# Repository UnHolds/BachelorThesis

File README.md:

# Bachelor Thesis

This is the repository of my bachelor thesis for the Software Engineering
bachelor at TU-Vienna.

## Structure

```
.
├── Code/
│   ├── AmpelSchaltung
│   ├── AudioBuffer
│   ├── AudioPlayer
│   ├── ExperimentI2CSpeakerSystem
│   ├── ExperimentNandGatter
│   ├── ExperimentNandGatter2
│   ├── ExperimentNandGatterDACControl
│   └── I2CSpeakerSystemSDCard
├── FreeCAD/
│   ├── Ampel
│   ├── AudioController
│   ├── Speaker_Housing
│   └── ...
├── KiCAD/
│   ├── AmpelSchaltung
│   ├── AudioController
│   ├── CabelAdapter
│   ├── ExperimentNAND
│   └── Speaker
├── LtSpice/
│   ├── Metastabile-NAND-Gatter
│   ├── i2c_speaker_amp
│   └── models
├── Tools
├── bachelorThesisObsidian
├── latex
└── slides
```

- `Code`: Contains the firmware of the different prototypes, the most important firmware are:
  - `AmpelSchaltung`: Firmware for the Ampelschaltung
  - `AudioBuffer`: Firmware of the audio buffer on the audio control PCB
  - `AudioPlayer`: Firmware of the audio player on the audio control PCB
- `FreeCAD`: contains the housing of the different demonstrators, and also 3D models that where used in assemblies.
  - `Ampel`: housing for the Ampelschaltung
  - `AudioController`: housing of the controller part of the audio demonstrator
  - `Speaker_Housing`: housing of the speaker part of the audio demonstrator
- `KiCAD`: contains the schematics and the PCB of the demonstrators
- `LtSpice`: contains the simulations and also the LtSpice model of the DAC.
- `Tools`: contains the tools that were used to evaluated data, display data or to generate audio files (`.bwav`)
- `bachelorThesisObsidian`: contains a lot of addition information and the development process. Can be seen as an extension of the thesis. To view the files it is encouraged to use [obsidian](https://obsidian.md/), but is also possible to just view the plain markdown files.
- `latex`: contains the raw latex files to build the thesis
- `slides`: contains the slides that are used in the prolog. (Important: This is a submodule and one needs to have access rights to the prolog repo to clone this repository)

# Demonstrators:

## Ampelschaltung

## Audioschaltung

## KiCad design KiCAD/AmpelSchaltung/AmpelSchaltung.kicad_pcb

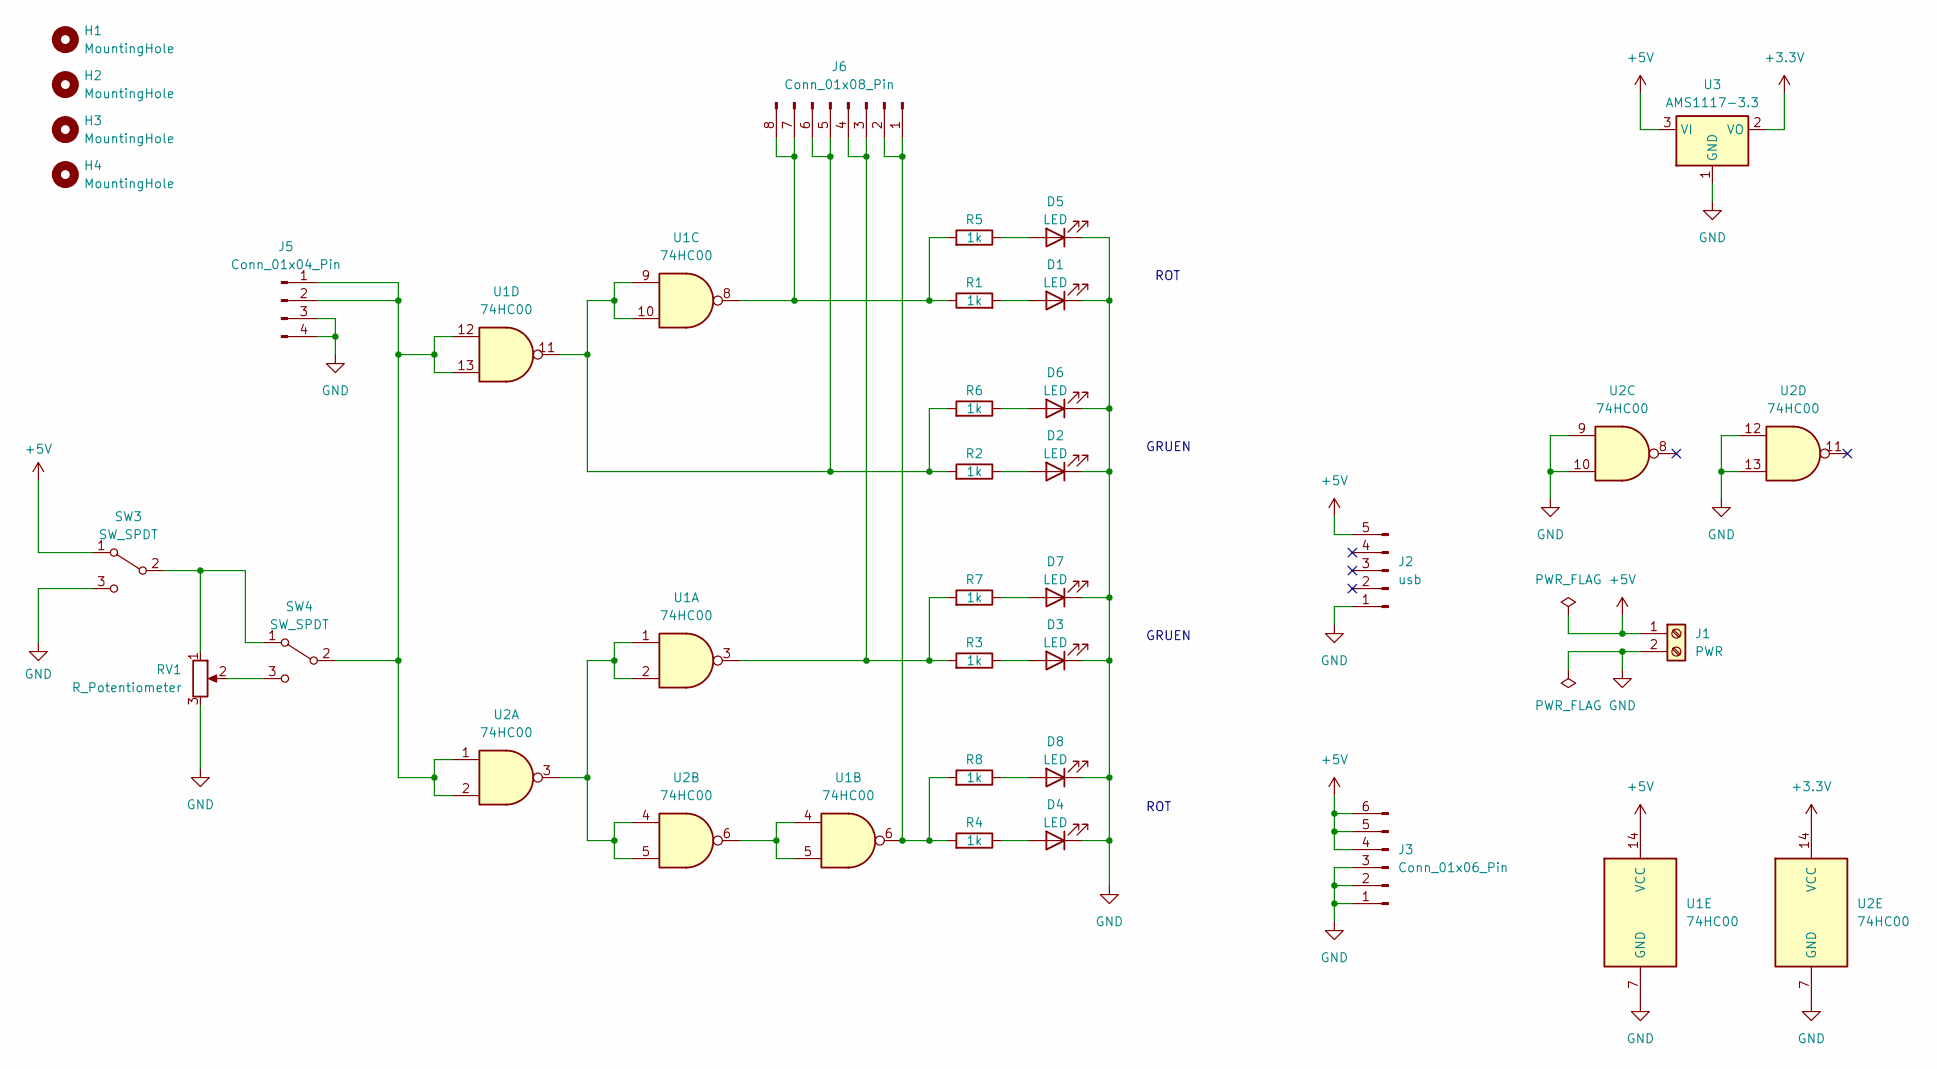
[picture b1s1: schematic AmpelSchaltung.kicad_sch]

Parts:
D1, D2, D3, D4, D5, D6, D7, D8: LED; LED_D5.0mm_Clear
H1, H2, H3, H4: MountingHole; MountingHole_3.2mm_M3
J1: PWR; TerminalBlock_MetzConnect_Type055_RT01502HDWU_1x02_P5.00mm_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
J2: usb; PinHeader_1x05_P2.54mm_Vertical
J3: Conn_01x06_Pin; PinHeader_1x06_P2.54mm_Vertical
J5: Conn_01x04_Pin; PinHeader_1x04_P2.54mm_Vertical
J6: Conn_01x08_Pin; PinHeader_1x08_P2.54mm_Vertical
R1, R2, R3, R4, R5, R6, R7, R8: 1k; R_0805_2012Metric_Pad1.20x1.40mm_HandSolder
RV1: R_Potentiometer; Potentiometer_Alpha_RD901F-40-00D_Single_Vertical
SW3, SW4: SW_SPDT; Goobay10020
U1, U2: 74HC00; DIP-14_W7.62mm_Socket
U3: AMS1117-3.3; SOT-223-3_TabPin2

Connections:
+3.3V: U2.14 (VCC), U3.2 (VO)
+5V: J1.1, J2.5, J3.4, J3.5, J3.6, SW3.1 (A), U1.14 (VCC), U3.3 (VI)
GND: D1.1 (K), D2.1 (K), D3.1 (K), D4.1 (K), D5.1 (K), D6.1 (K), D7.1 (K), D8.1 (K), J1.2, J2.1, J3.1, J3.2, J3.3, J5.3, J5.4, RV1.3, SW3.3 (C), U1.7 (GND), U2.7 (GND), U2.9, U2.10, U2.12, U2.13, U3.1 (GND)
unnamed: D1.2 (A), R1.2
unnamed: D2.2 (A), R2.1
unnamed: D3.2 (A), R3.1
unnamed: D4.2 (A), R4.1
unnamed: D5.2 (A), R5.1
unnamed: D6.2 (A), R6.1
unnamed: D7.2 (A), R7.1
unnamed: D8.2 (A), R8.1
unnamed: J5.1, J5.2, SW4.2 (B), U1.12, U1.13, U2.1, U2.2
unnamed: J6.1, J6.2, R4.2, R8.2, U1.6
unnamed: J6.3, J6.4, R3.2, R7.2, U1.3
unnamed: J6.5, J6.6, R2.2, R6.2, U1.9, U1.10, U1.11
unnamed: J6.7, J6.8, R1.1, R5.2, U1.8
unnamed: RV1.1, SW3.2 (B), SW4.1 (A)
unnamed: RV1.2, SW4.3 (C)
unnamed: U1.1, U1.2, U2.3, U2.4, U2.5
unnamed: U1.4, U1.5, U2.6

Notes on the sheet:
ROT
GRUEN

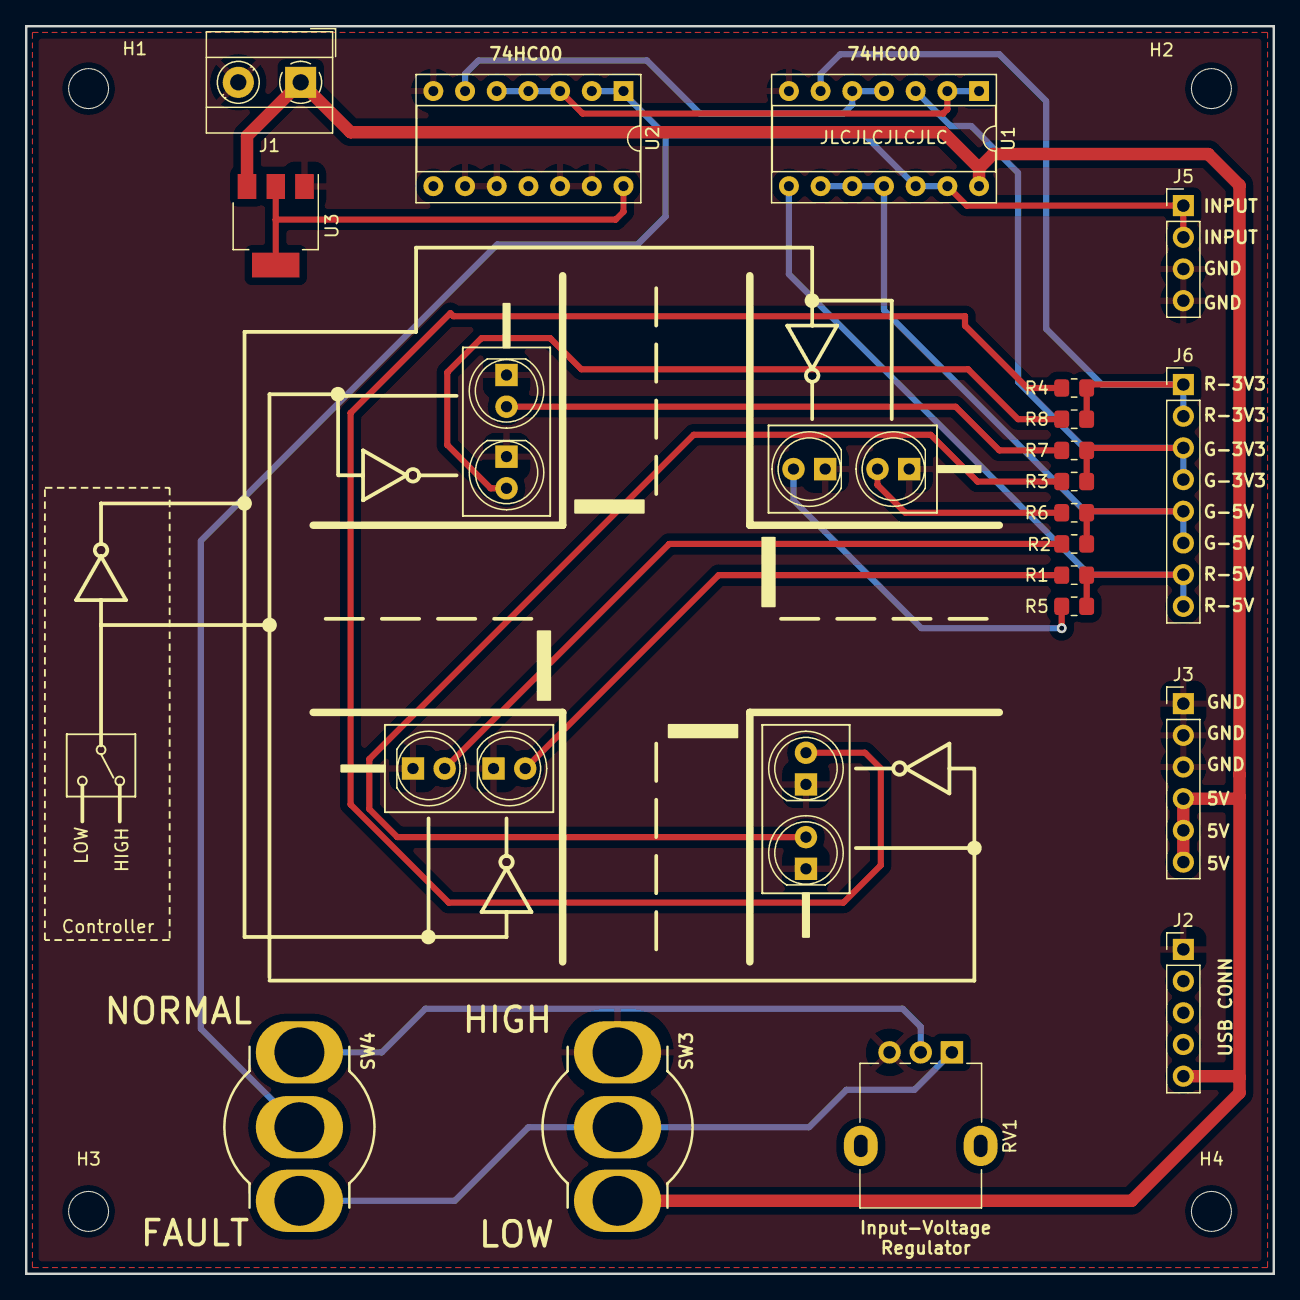
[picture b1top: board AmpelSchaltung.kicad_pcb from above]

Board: 2 copper layers, 100.0 x 100.0 mm, 31 parts (0 on the bottom side), 20 nets.

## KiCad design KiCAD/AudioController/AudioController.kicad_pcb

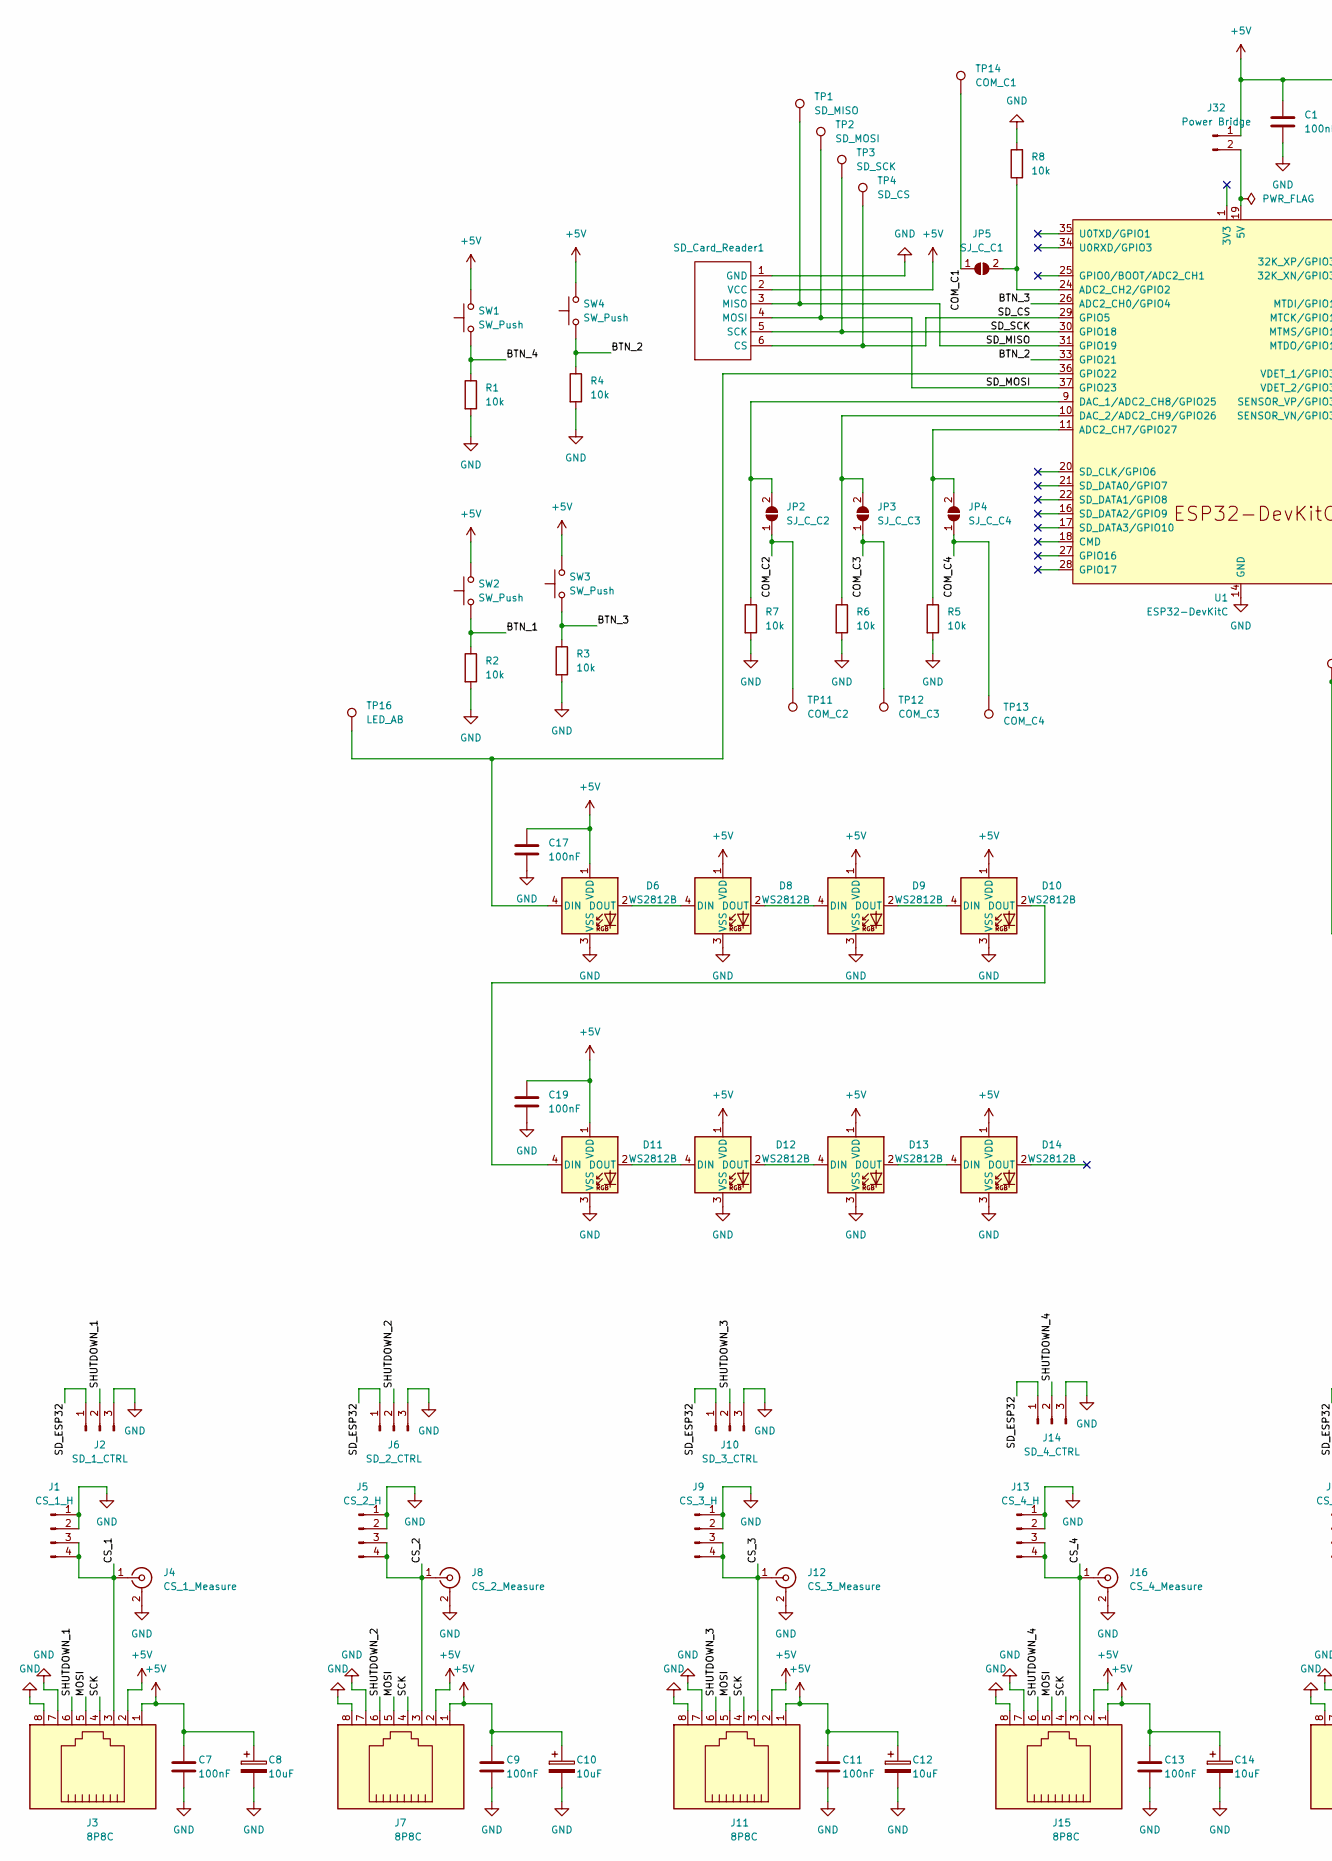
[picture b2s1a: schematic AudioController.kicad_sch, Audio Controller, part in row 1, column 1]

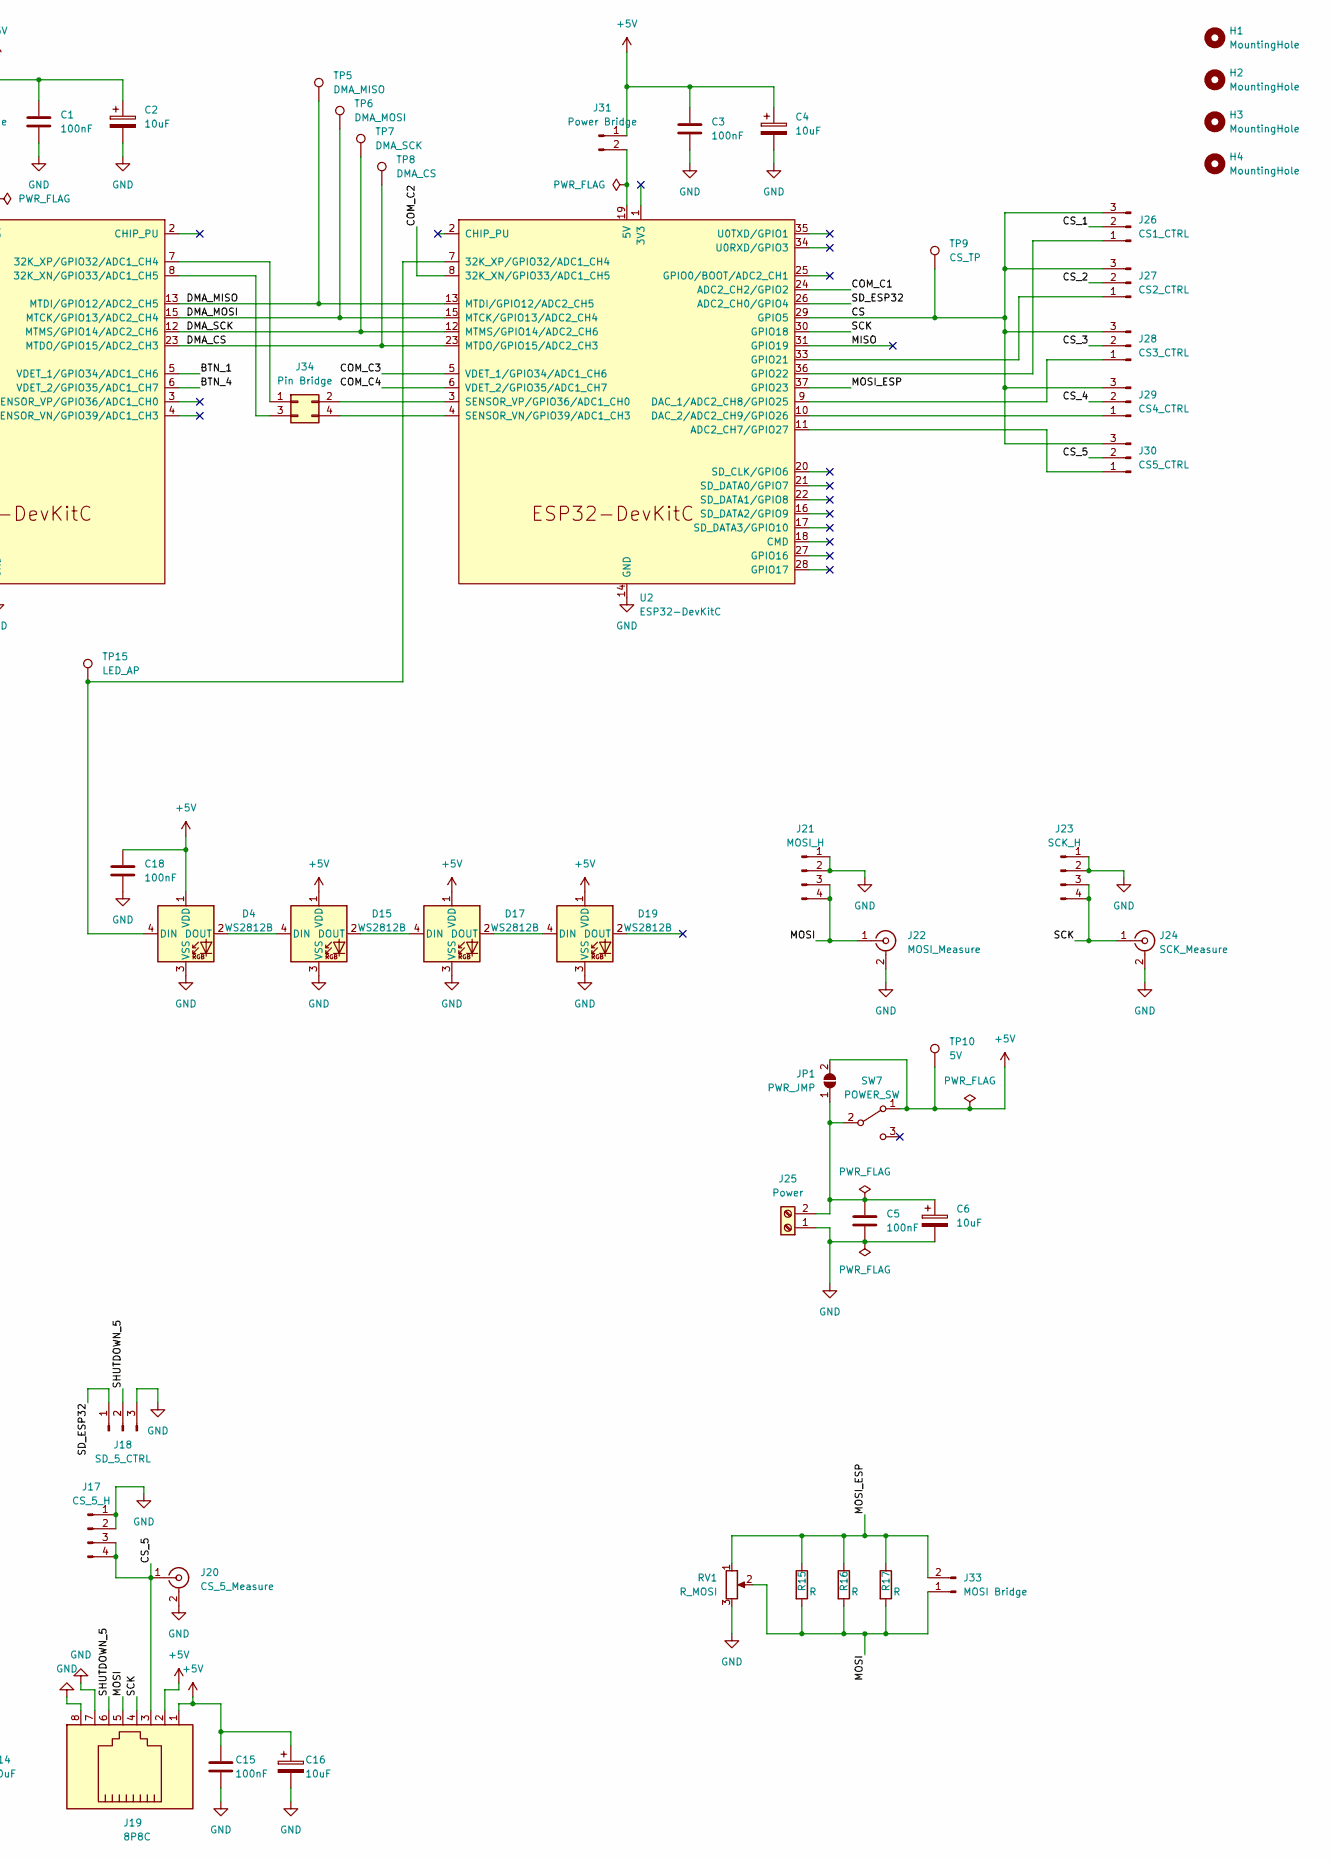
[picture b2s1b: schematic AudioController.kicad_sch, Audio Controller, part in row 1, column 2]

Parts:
C1, C3, C5, C7, C9, C11, C13, C15, C17, C18, C19: 100nF; C_1206_3216Metric_Pad1.33x1.80mm_HandSolder
C2, C4, C6, C8, C10, C12, C14, C16: 10uF; CP_Radial_D5.0mm_P2.50mm
D4, D6, D8, D9, D10, D11, D12, D13, D14, D15, D17, D19: WS2812B; LED_WS2812B_PLCC4_5.0x5.0mm_P3.2mm
H1, H2, H3, H4: MountingHole; MountingHole_3.2mm_M3
J1: CS_1_H; PinHeader_1x04_P2.54mm_Vertical
J2: SD_1_CTRL; PinHeader_1x03_P2.54mm_Vertical
J3, J7, J11, J15, J19: 8P8C; RJ45_Amphenol_54602-x08_Horizontal_Custom
J4: CS_1_Measure; BNC_Connector
J5: CS_2_H; PinHeader_1x04_P2.54mm_Vertical
J6: SD_2_CTRL; PinHeader_1x03_P2.54mm_Vertical
J8: CS_2_Measure; BNC_Connector
J9: CS_3_H; PinHeader_1x04_P2.54mm_Vertical
J10: SD_3_CTRL; PinHeader_1x03_P2.54mm_Vertical
J12: CS_3_Measure; BNC_Connector
J13: CS_4_H; PinHeader_1x04_P2.54mm_Vertical
J14: SD_4_CTRL; PinHeader_1x03_P2.54mm_Vertical
J16: CS_4_Measure; BNC_Connector
J17: CS_5_H; PinHeader_1x04_P2.54mm_Vertical
J18: SD_5_CTRL; PinHeader_1x03_P2.54mm_Vertical
J20: CS_5_Measure; BNC_Connector
J21: MOSI_H; PinHeader_1x04_P2.54mm_Vertical
J22: MOSI_Measure; BNC_Connector
J23: SCK_H; PinHeader_1x04_P2.54mm_Vertical
J24: SCK_Measure; BNC_Connector
J25: Power; TerminalBlock_MetzConnect_Type055_RT01502HDWU_1x02_P5.00mm_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
J26: CS1_CTRL; PinHeader_1x03_P2.54mm_Vertical
J27: CS2_CTRL; PinHeader_1x03_P2.54mm_Vertical
J28: CS3_CTRL; PinHeader_1x03_P2.54mm_Vertical
J29: CS4_CTRL; PinHeader_1x03_P2.54mm_Vertical
J30: CS5_CTRL; PinHeader_1x03_P2.54mm_Vertical
J31, J32: Power Bridge; PinHeader_1x02_P2.54mm_Vertical
J33: MOSI Bridge; PinHeader_1x02_P2.54mm_Vertical
J34: Pin Bridge; PinHeader_2x02_P2.54mm_Vertical
JP1: PWR_JMP; SolderJumper-2_P1.3mm_Open_Pad1.0x1.5mm
JP2: SJ_C_C2; SolderJumper-2_P1.3mm_Open_Pad1.0x1.5mm
JP3: SJ_C_C3; SolderJumper-2_P1.3mm_Open_Pad1.0x1.5mm
JP4: SJ_C_C4; SolderJumper-2_P1.3mm_Open_Pad1.0x1.5mm
JP5: SJ_C_C1; SolderJumper-2_P1.3mm_Open_Pad1.0x1.5mm
R1, R2, R3, R4, R5, R6, R7, R8: 10k; R_0805_2012Metric_Pad1.20x1.40mm_HandSolder
R15, R16, R17: R; R_0805_2012Metric_Pad1.20x1.40mm_HandSolder
RV1: R_MOSI; Potentiometer_Piher_PT-6-V_Vertical
SD_Card_Reader1: SD-Card_Adapter
SW1, SW2, SW3, SW4: SW_Push; SW_PUSH_6mm
SW7: POWER_SW; Goobay10020
TP1: SD_MISO; TestPoint_Pad_D3.0mm
TP2: SD_MOSI; TestPoint_Pad_D3.0mm
TP3: SD_SCK; TestPoint_Pad_D3.0mm
TP4: SD_CS; TestPoint_Pad_D3.0mm
TP5: DMA_MISO; TestPoint_Pad_D3.0mm
TP6: DMA_MOSI; TestPoint_Pad_D3.0mm
TP7: DMA_SCK; TestPoint_Pad_D3.0mm
TP8: DMA_CS; TestPoint_Pad_D3.0mm
TP9: CS_TP; TestPoint_Pad_D3.0mm
TP10: 5V; TestPoint_Pad_D3.0mm
TP11: COM_C2; TestPoint_Pad_D3.0mm
TP12: COM_C3; TestPoint_Pad_D3.0mm
TP13: COM_C4; TestPoint_Pad_D3.0mm
TP14: COM_C1; TestPoint_Pad_D3.0mm
TP15: LED_AP; TestPoint_Pad_D3.0mm
TP16: LED_AB; TestPoint_Pad_D3.0mm
U1, U2: ESP32-DevKitC

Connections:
+5V: C1.1, C2.1, C3.1, C4.1, C7.1, C8.1, C9.1, C10.1, C11.1, C12.1, C13.1, C14.1, C15.1, C16.1, C17.1, C18.1, C19.1, D4.1 (VDD), D6.1 (VDD), D8.1 (VDD), D9.1 (VDD), D10.1 (VDD), D11.1 (VDD), D12.1 (VDD), D13.1 (VDD), D14.1 (VDD), D15.1 (VDD), D17.1 (VDD), D19.1 (VDD), J3.1, J3.2, J7.1, J7.2, J11.1, J11.2, J15.1, J15.2, J19.1, J19.2, J31.1, J32.1, JP1.2 (B), SD_Card_Reader1.2 (VCC), SW1.2, SW2.2, SW3.2, SW4.2, SW7.1 (A), TP10.1
/BTN_1: R2.1, SW2.1, U1.5 (VDET_1/GPIO34/ADC1_CH6)
/BTN_2: R4.1, SW4.1, U1.33 (GPIO21)
/BTN_3: R3.1, SW3.1, U1.26 (ADC2_CH0/GPIO4)
/BTN_4: R1.1, SW1.1, U1.6 (VDET_2/GPIO35/ADC1_CH7)
/COM_C1: JP5.1 (A), TP14.1, U2.24 (ADC2_CH2/GPIO2)
/COM_C2: JP2.1 (A), TP11.1, U2.8 (32K_XN/GPIO33/ADC1_CH5)
/COM_C3: JP3.1 (A), TP12.1, U2.5 (VDET_1/GPIO34/ADC1_CH6)
/COM_C4: JP4.1 (A), TP13.1, U2.6 (VDET_2/GPIO35/ADC1_CH7)
/CS: J26.3, J27.3, J28.3, J29.3, J30.3, TP9.1, U2.29 (GPIO5)
/CS_1: J1.3, J1.4, J3.3, J4.1 (In), J26.2
/CS_2: J5.3, J5.4, J7.3, J8.1 (In), J27.2
/CS_3: J9.3, J9.4, J11.3, J12.1 (In), J28.2
/CS_4: J13.3, J13.4, J15.3, J16.1 (In), J29.2
/CS_5: J17.3, J17.4, J19.3, J20.1 (In), J30.2
/DMA_CS: TP8.1, U1.23 (MTDO/GPIO15/ADC2_CH3), U2.23 (MTDO/GPIO15/ADC2_CH3)
/DMA_MISO: TP5.1, U1.13 (MTDI/GPIO12/ADC2_CH5), U2.13 (MTDI/GPIO12/ADC2_CH5)
/DMA_MOSI: TP6.1, U1.15 (MTCK/GPIO13/ADC2_CH4), U2.15 (MTCK/GPIO13/ADC2_CH4)
/DMA_SCK: TP7.1, U1.12 (MTMS/GPIO14/ADC2_CH6), U2.12 (MTMS/GPIO14/ADC2_CH6)
/MISO: U2.31 (GPIO19)
/MOSI: J3.5, J7.5, J11.5, J15.5, J19.5, J21.3, J21.4, J22.1 (In), J33.1, R15.2, R16.2, R17.2, RV1.2
/MOSI_ESP: J33.2, R15.1, R16.1, R17.1, RV1.1, U2.37 (GPIO23)
/SCK: J3.4, J7.4, J11.4, J15.4, J19.4, J23.3, J23.4, J24.1 (In), U2.30 (GPIO18)
/SD_CS: SD_Card_Reader1.6 (CS), TP4.1, U1.29 (GPIO5)
/SD_ESP32: J2.1, J6.1, J10.1, J14.1, J18.1, U2.26 (ADC2_CH0/GPIO4)
/SD_MISO: SD_Card_Reader1.3 (MISO), TP1.1, U1.31 (GPIO19)
/SD_MOSI: SD_Card_Reader1.4 (MOSI), TP2.1, U1.37 (GPIO23)
/SD_SCK: SD_Card_Reader1.5 (SCK), TP3.1, U1.30 (GPIO18)
/SHUTDOWN_1: J2.2, J3.6
/SHUTDOWN_2: J6.2, J7.6
/SHUTDOWN_3: J10.2, J11.6
/SHUTDOWN_4: J14.2, J15.6
/SHUTDOWN_5: J18.2, J19.6
GND: C1.2, C2.2, C3.2, C4.2, C5.2, C6.2, C7.2, C8.2, C9.2, C10.2, C11.2, C12.2, C13.2, C14.2, C15.2, C16.2, C17.2, C18.2, C19.2, D4.3 (VSS), D6.3 (VSS), D8.3 (VSS), D9.3 (VSS), D10.3 (VSS), D11.3 (VSS), D12.3 (VSS), D13.3 (VSS), D14.3 (VSS), D15.3 (VSS), D17.3 (VSS), D19.3 (VSS), J1.1, J1.2, J2.3, J3.7, J3.8, J4.2 (Ext), J5.1, J5.2, J6.3, J7.7, J7.8, J8.2 (Ext), J9.1, J9.2, J10.3, J11.7, J11.8, J12.2 (Ext), J13.1, J13.2, J14.3, J15.7, J15.8, J16.2 (Ext), J17.1, J17.2, J18.3, J19.7, J19.8, J20.2 (Ext), J21.1, J21.2, J22.2 (Ext), J23.1, J23.2, J24.2 (Ext), J25.1, R1.2, R2.2, R3.2, R4.2, R5.2, R6.2, R7.2, R8.2, RV1.3, SD_Card_Reader1.1 (GND), U1.14 (GND), U1.32 (GND), U1.38 (GND), U2.14 (GND), U2.32 (GND), U2.38 (GND)
unnamed: D4.4 (DIN), TP15.1, U2.7 (32K_XP/GPIO32/ADC1_CH4)
unnamed: D6.4 (DIN), TP16.1, U1.36 (GPIO22)
unnamed: D6.2 (DOUT), D8.4 (DIN)
unnamed: D8.2 (DOUT), D9.4 (DIN)
unnamed: D9.2 (DOUT), D10.4 (DIN)
unnamed: D10.2 (DOUT), D11.4 (DIN)
unnamed: D11.2 (DOUT), D12.4 (DIN)
unnamed: D12.2 (DOUT), D13.4 (DIN)
unnamed: D13.2 (DOUT), D14.4 (DIN)
unnamed: D4.2 (DOUT), D15.4 (DIN)
unnamed: D15.2 (DOUT), D17.4 (DIN)
unnamed: D17.2 (DOUT), D19.4 (DIN)
unnamed: C5.1, C6.1, J25.2, JP1.1 (A), SW7.2 (B)
unnamed: J26.1, U2.36 (GPIO22)
unnamed: J27.1, U2.33 (GPIO21)
unnamed: J28.1, U2.9 (DAC_1/ADC2_CH8/GPIO25)
unnamed: J29.1, U2.10 (DAC_2/ADC2_CH9/GPIO26)
unnamed: J30.1, U2.11 (ADC2_CH7/GPIO27)
unnamed: J31.2, U2.19 (5V)
unnamed: J32.2, U1.19 (5V)
unnamed: J34.1, U1.7 (32K_XP/GPIO32/ADC1_CH4)
unnamed: J34.2, U2.3 (SENSOR_VP/GPIO36/ADC1_CH0)
unnamed: J34.3, U1.8 (32K_XN/GPIO33/ADC1_CH5)
unnamed: J34.4, U2.4 (SENSOR_VN/GPIO39/ADC1_CH3)
unnamed: JP2.2 (B), R7.1, U1.9 (DAC_1/ADC2_CH8/GPIO25)
unnamed: JP3.2 (B), R6.1, U1.10 (DAC_2/ADC2_CH9/GPIO26)
unnamed: JP4.2 (B), R5.1, U1.11 (ADC2_CH7/GPIO27)
unnamed: JP5.2 (B), R8.1, U1.24 (ADC2_CH2/GPIO2)

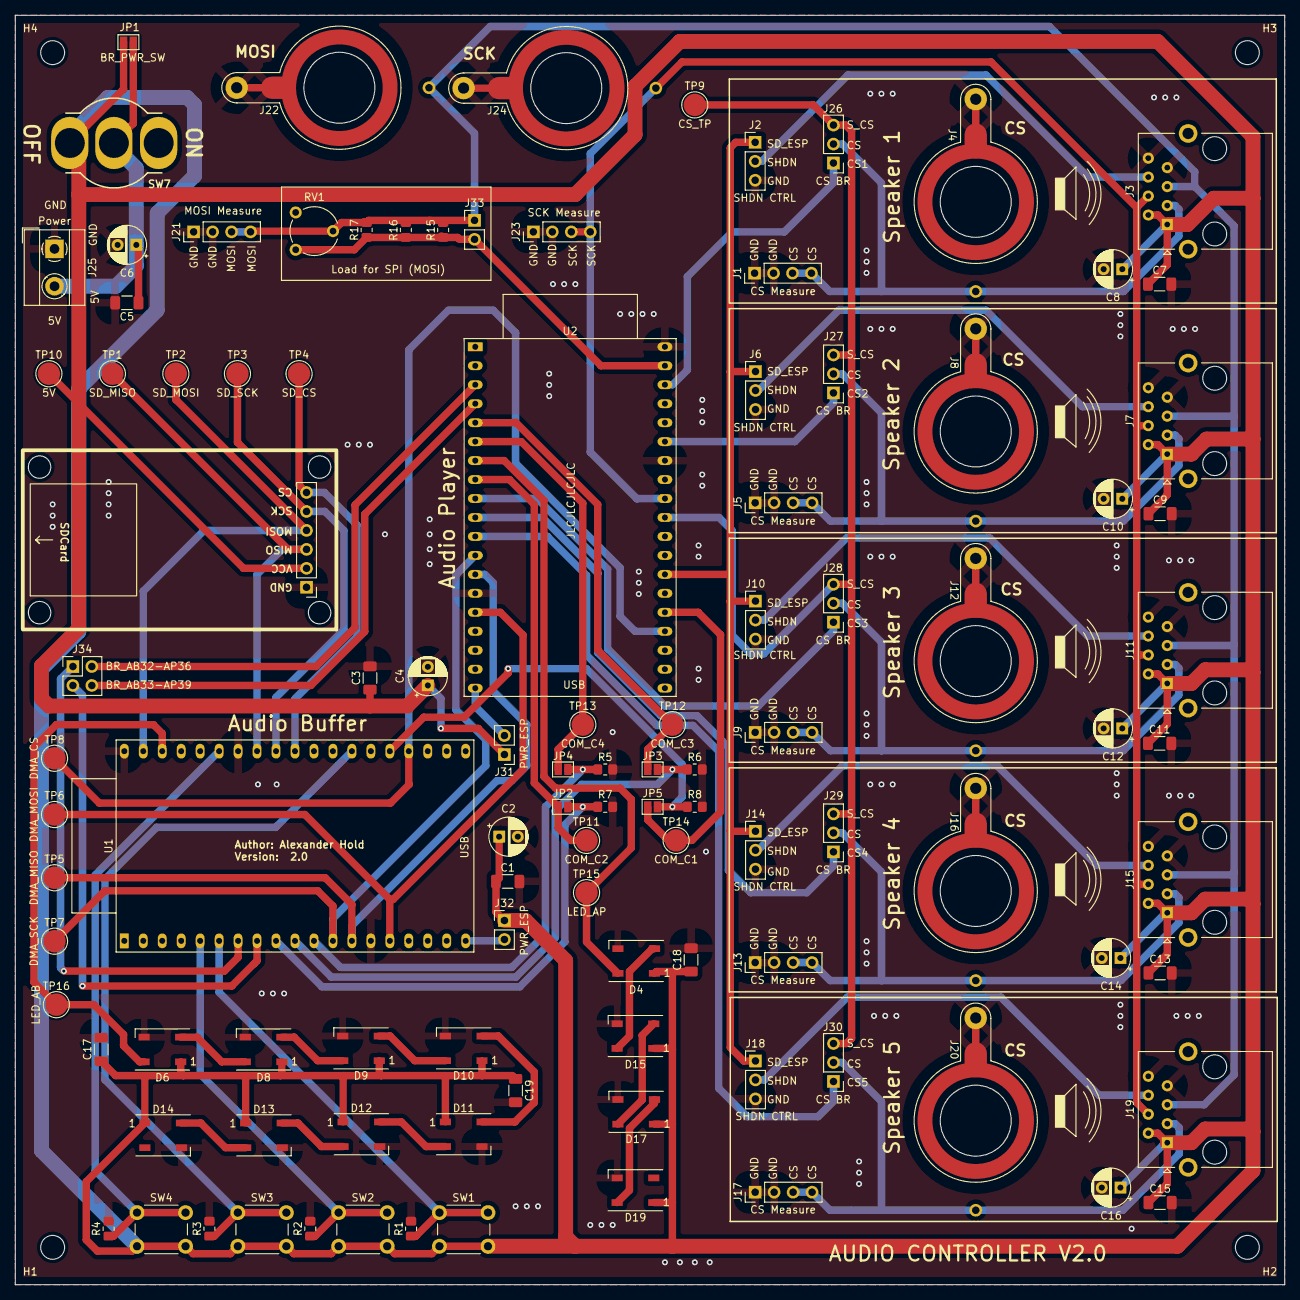
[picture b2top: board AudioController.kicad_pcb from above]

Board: 2 copper layers, 170.0 x 170.0 mm, 110 parts (0 on the bottom side), 61 nets.

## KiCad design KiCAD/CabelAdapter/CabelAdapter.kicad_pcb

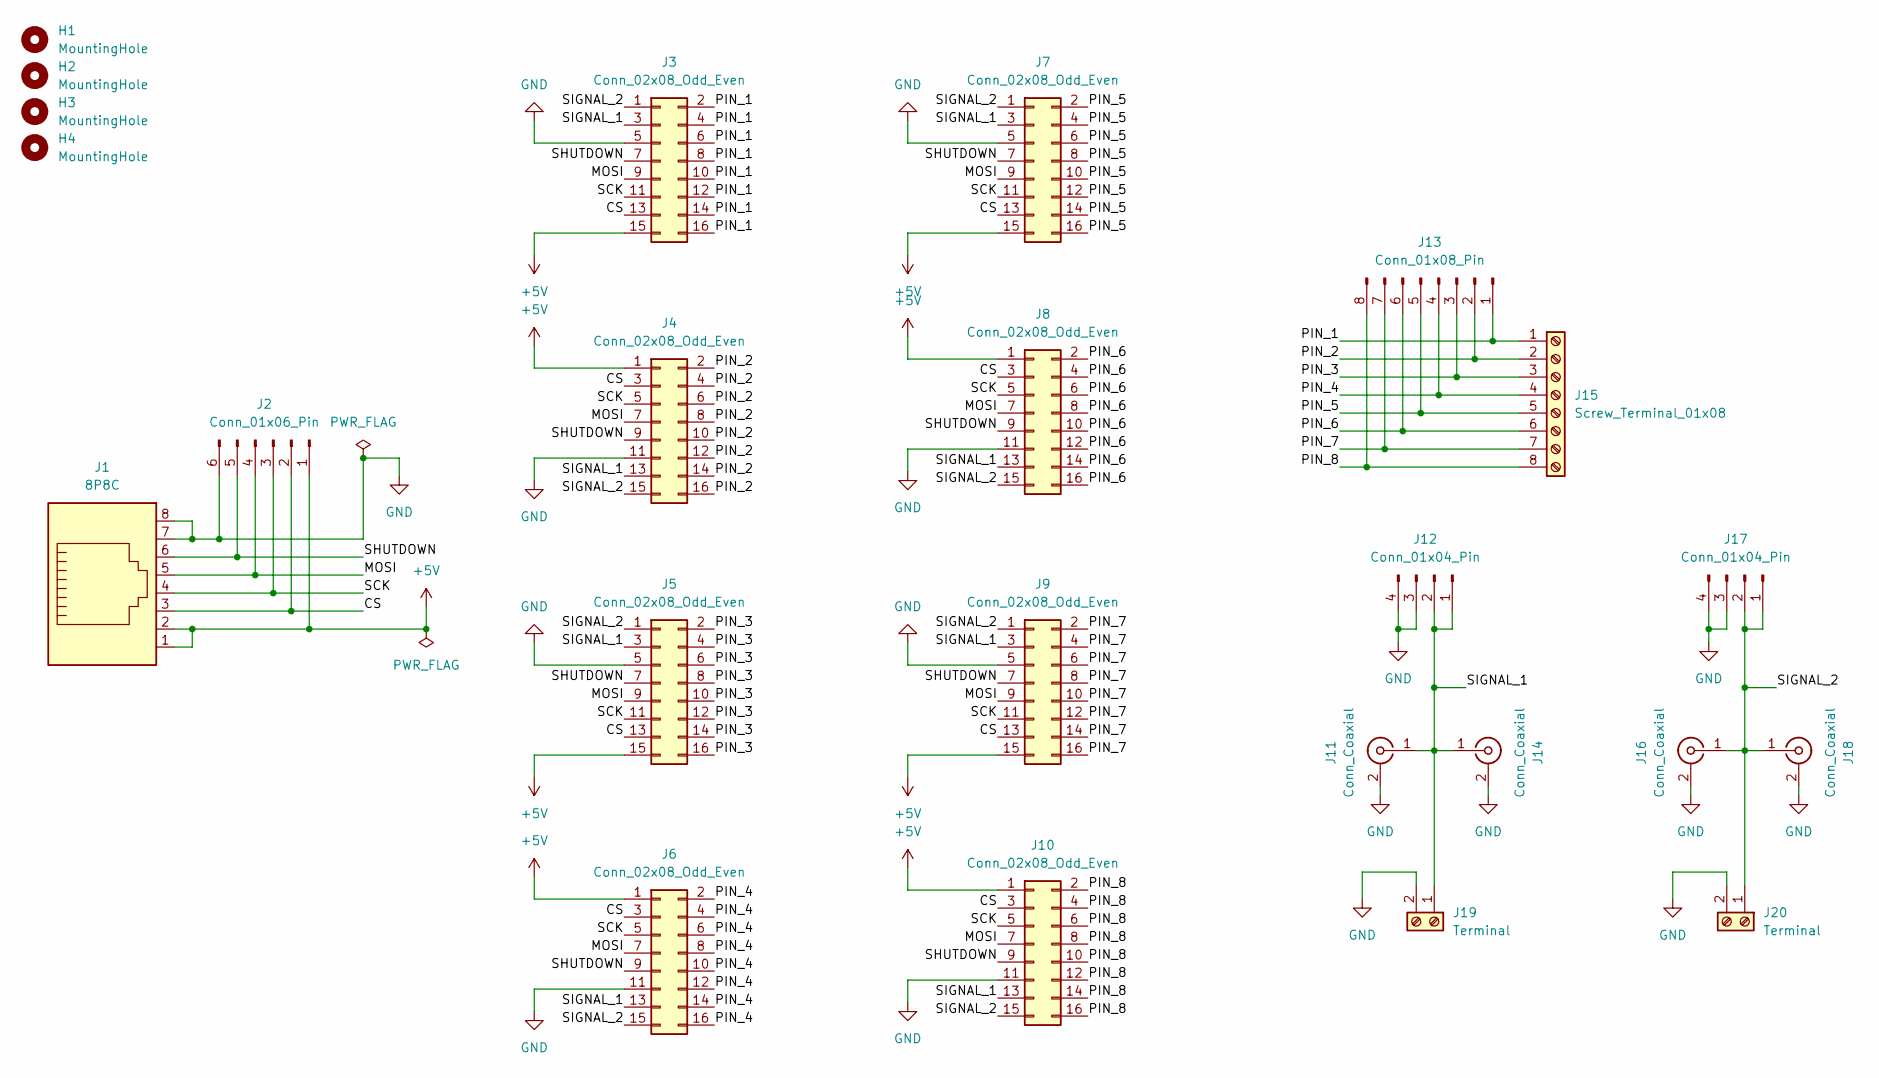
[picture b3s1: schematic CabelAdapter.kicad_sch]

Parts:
H1, H2, H3, H4: MountingHole; MountingHole_3.2mm_M3
J1: 8P8C; RJ45_Amphenol_54602-x08_Horizontal_Custom
J2: Conn_01x06_Pin; PinSocket_1x06_P2.54mm_Vertical
J3, J4, J5, J6, J7, J8, J9, J10: Conn_02x08_Odd_Even; PinSocket_2x08_P2.54mm_Vertical
J11, J14, J16, J18: Conn_Coaxial; BNC_Connector
J12, J17: Conn_01x04_Pin; PinSocket_1x04_P2.54mm_Vertical
J13: Conn_01x08_Pin; PinSocket_1x08_P2.54mm_Vertical
J15: Screw_Terminal_01x08; ScrewConnector8
J19, J20: Terminal; TerminalBlock_MetzConnect_Type055_RT01502HDWU_1x02_P5.00mm_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

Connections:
+5V: J1.1, J1.2, J2.1, J3.15, J4.1, J5.15, J6.1, J7.15, J8.1, J9.15, J10.1
/CS: J1.3, J2.2, J3.13, J4.3, J5.13, J6.3, J7.13, J8.3, J9.13, J10.3
/MOSI: J1.5, J2.4, J3.9, J4.7, J5.9, J6.7, J7.9, J8.7, J9.9, J10.7
/PIN_1: J3.2, J3.4, J3.6, J3.8, J3.10, J3.12, J3.14, J3.16, J13.1, J15.1
/PIN_2: J4.2, J4.4, J4.6, J4.8, J4.10, J4.12, J4.14, J4.16, J13.2, J15.2
/PIN_3: J5.2, J5.4, J5.6, J5.8, J5.10, J5.12, J5.14, J5.16, J13.3, J15.3
/PIN_4: J6.2, J6.4, J6.6, J6.8, J6.10, J6.12, J6.14, J6.16, J13.4, J15.4
/PIN_5: J7.2, J7.4, J7.6, J7.8, J7.10, J7.12, J7.14, J7.16, J13.5, J15.5
/PIN_6: J8.2, J8.4, J8.6, J8.8, J8.10, J8.12, J8.14, J8.16, J13.6, J15.6
/PIN_7: J9.2, J9.4, J9.6, J9.8, J9.10, J9.12, J9.14, J9.16, J13.7, J15.7
/PIN_8: J10.2, J10.4, J10.6, J10.8, J10.10, J10.12, J10.14, J10.16, J13.8, J15.8
/SCK: J1.4, J2.3, J3.11, J4.5, J5.11, J6.5, J7.11, J8.5, J9.11, J10.5
/SHUTDOWN: J1.6, J2.5, J3.7, J4.9, J5.7, J6.9, J7.7, J8.9, J9.7, J10.9
/SIGNAL_1: J3.3, J4.13, J5.3, J6.13, J7.3, J8.13, J9.3, J10.13, J11.1 (In), J12.1, J12.2, J14.1 (In), J19.1
/SIGNAL_2: J3.1, J4.15, J5.1, J6.15, J7.1, J8.15, J9.1, J10.15, J16.1 (In), J17.1, J17.2, J18.1 (In), J20.1
GND: J1.7, J1.8, J2.6, J3.5, J4.11, J5.5, J6.11, J7.5, J8.11, J9.5, J10.11, J11.2 (Ext), J12.3, J12.4, J14.2 (Ext), J16.2 (Ext), J17.3, J17.4, J18.2 (Ext), J19.2, J20.2

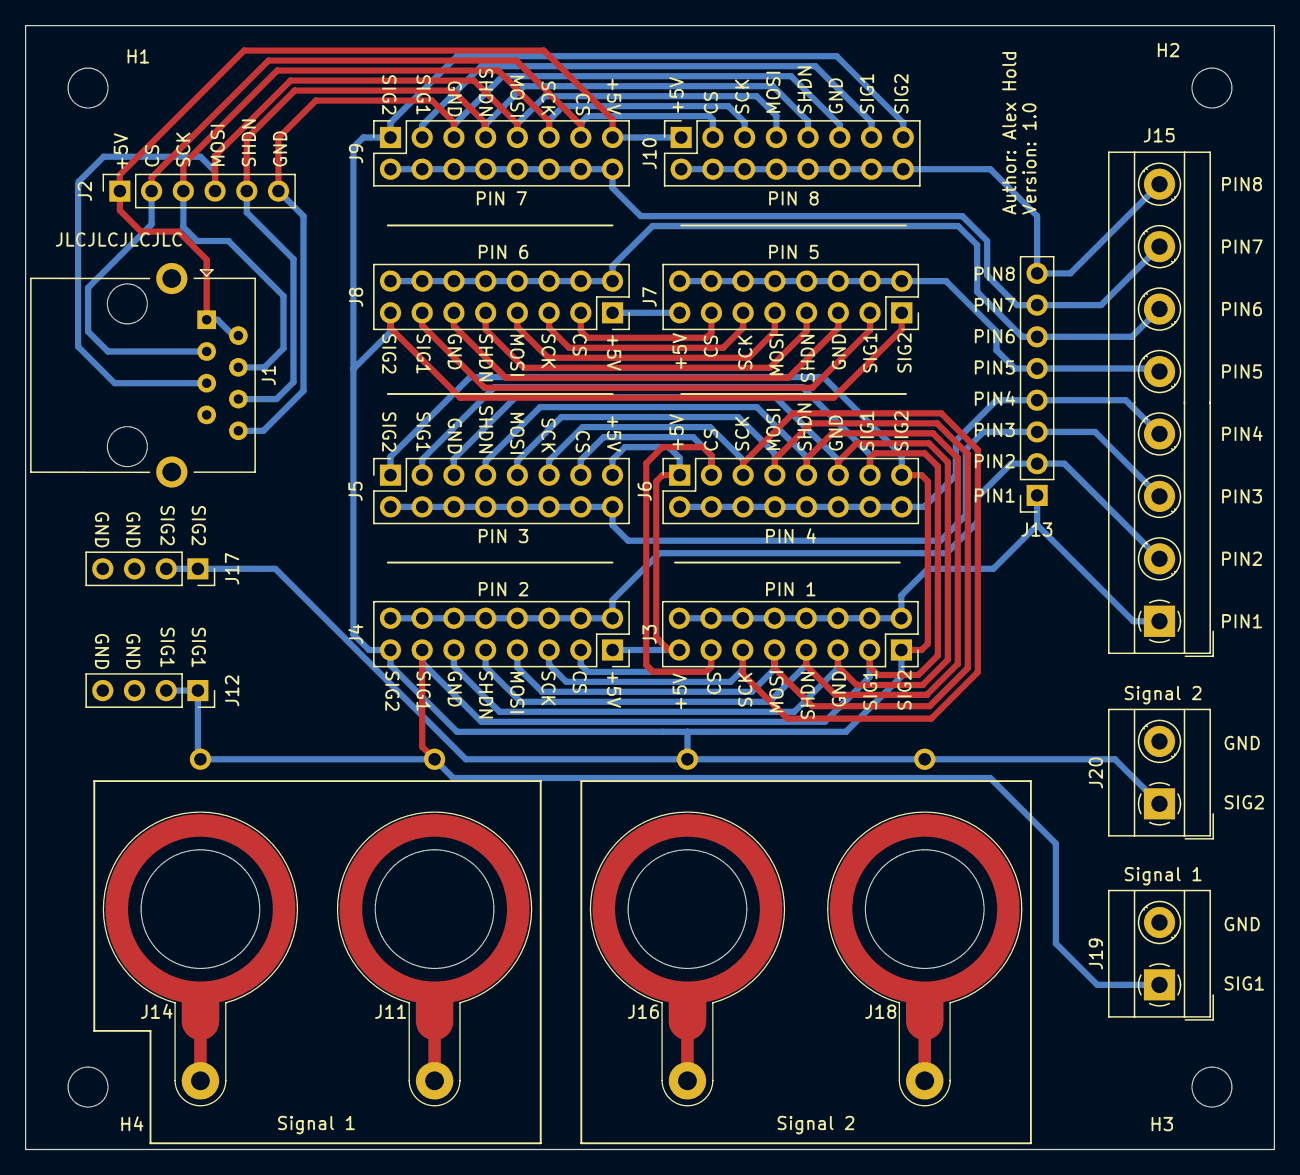
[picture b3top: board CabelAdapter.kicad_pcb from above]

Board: 4 copper layers, 100.0 x 90.0 mm, 24 parts (0 on the bottom side), 16 nets.
